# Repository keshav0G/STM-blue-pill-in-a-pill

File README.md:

# STM-blue-pill-in-a-pill
devboard for STM32f103c8tx series boards aka the blue pill in the shape of a pill

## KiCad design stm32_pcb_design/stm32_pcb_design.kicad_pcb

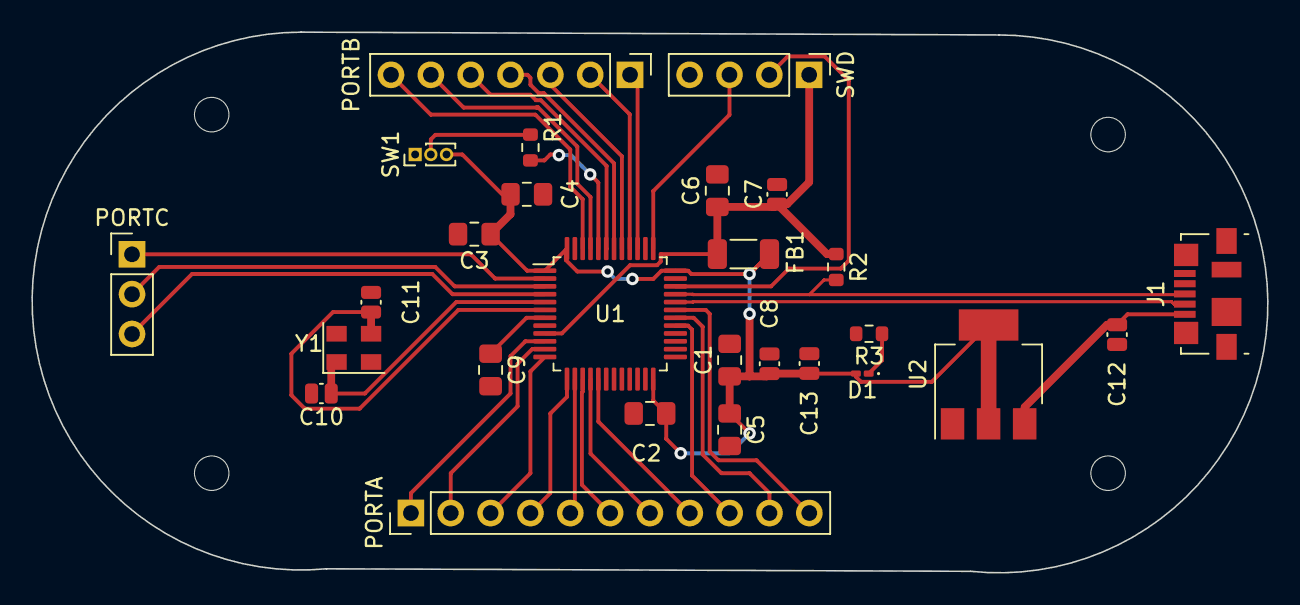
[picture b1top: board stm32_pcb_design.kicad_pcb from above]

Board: 2 copper layers, 78.8 x 34.5 mm, 31 parts (0 on the bottom side), 35 nets.

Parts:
C1, C2, C3, C4, C9: 100n; C_0805_2012Metric_Pad1.18x1.45mm_HandSolder
C5: 10u; C_0805_2012Metric_Pad1.18x1.45mm_HandSolder
C6: 10n; C_0805_2012Metric_Pad1.18x1.45mm_HandSolder
C7, C8: 1u; C_0504_1310Metric_Pad0.83x1.28mm_HandSolder
C10, C11: 10p; C_0504_1310Metric_Pad0.83x1.28mm_HandSolder
C12, C13: 22u; C_0504_1310Metric_Pad0.83x1.28mm_HandSolder
D1: LED; LED_0201_0603Metric_Pad0.64x0.40mm_HandSolder
FB1: 120R; L_1206_3216Metric_Pad1.22x1.90mm_HandSolder
H1, H2, H3, H4: MountingHole; MountingHole_2.2mm_M2
J1: USB_B_Micro; USB_Micro-B_Molex_47346-0001
PORTA: PORTA; PinHeader_1x11_P2.54mm_Vertical
PORTB: Conn_01x07_Pin; PinHeader_1x07_P2.54mm_Vertical
PORTC: PORTC; PinHeader_1x03_P2.54mm_Vertical
R1: 10k; R_0603_1608Metric
R2, R3: 1k5; R_0603_1608Metric
SW1: SW_SPDT; PinHeader_1x03_P1.00mm_Vertical
SWD: Conn_01x04_Pin; PinHeader_1x04_P2.54mm_Vertical
U1: STM32F103C8Tx; LQFP-48_7x7mm_P0.5mm
U2: AMS1117-3.3; SOT-223-3_TabPin2
Y1: 16MHz; Crystal_SMD_EuroQuartz_MT-4Pin_3.2x2.5mm

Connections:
+3.3V: C1.1, C2.1, C3.1, C4.1, C5.1, C8.1, C13.1, D1.2 (A), FB1.2, SW1.3 (C), U1.1 (VBAT), U1.24 (VDD), U1.36 (VDD), U1.48 (VDD), U2.2 (VO)
+3.3VA: C6.1, C7.1, FB1.1, R2.1, SWD.1, U1.9 (VDDA)
/BOOT0: R1.2, U1.44 (BOOT0)
/HSE_IN: C10.1, U1.5 (PD0), Y1.1
/HSE_OUT: C11.1, U1.6 (PD1), Y1.3
/NRST: C9.1, U1.7 (NRST)
/SWCLK: SWD.3, U1.37 (PA14)
/SWDIO: SWD.2, U1.34 (PA13)
/USB_D+: J1.3 (D+), R2.2, U1.33 (PA12)
/USB_D-: J1.2 (D-), U1.32 (PA11)
/sw_boot0: R1.1, SW1.2 (B)
GND: C1.2, C2.2, C3.2, C4.2, C5.2, C6.2, C7.2, C8.2, C9.2, C10.2, C11.2, C12.2, C13.2, J1.5 (GND), R3.2, SW1.1 (A), SWD.4, U1.8 (VSSA), U1.23 (VSS), U1.35 (VSS), U1.47 (VSS), U2.1 (GND), Y1.2, Y1.4
unnamed: D1.1 (K), R3.1
unnamed: PORTB.1, U1.39 (PB3)
unnamed: PORTB.2, U1.40 (PB4)
unnamed: PORTB.3, U1.41 (PB5)
unnamed: PORTB.4, U1.42 (PB6)
unnamed: PORTB.5, U1.43 (PB7)
unnamed: PORTB.6, U1.45 (PB8)
unnamed: PORTB.7, U1.46 (PB9)
unnamed: PORTA.1, U1.10 (PA0)
unnamed: PORTA.2, U1.11 (PA1)
unnamed: PORTA.3, U1.12 (PA2)
unnamed: PORTA.4, U1.13 (PA3)
unnamed: PORTA.5, U1.14 (PA4)
unnamed: PORTA.6, U1.15 (PA5)
unnamed: PORTA.7, U1.16 (PA6)
unnamed: PORTA.8, U1.17 (PA7)
unnamed: PORTA.9, U1.29 (PA8)
unnamed: PORTA.10, U1.30 (PA9)
unnamed: PORTA.11, U1.31 (PA10)
unnamed: PORTC.1, U1.2 (PC13)
unnamed: PORTC.2, U1.3 (PC14)
unnamed: PORTC.3, U1.4 (PC15)
VBUS: C12.1, J1.1 (VBUS), U2.3 (VI)
